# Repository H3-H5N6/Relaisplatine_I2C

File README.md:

# Beschreibung

8-fach Relaisplatine, die über I²C angesteuert wird. Die Relais werden dabei über eine separate Spannung versorgt.

Die I²C-Adresse muss durch entsprechende Brücken bei A0 - bis A2 ausgeält werden. Die Grundadresse des PCF 8475 ist 0x40 und de
ie des PCF 8475 ist 0x70.

Die LEDs bei den Relais leuchten, wenn die Relais in Ruhe sind. Des weiteren gibt es zwei Power-LEDs, einmal für die 5V vom I²C und einaml für die 5/12V der Relais.

Der Interrupt-Pin ist herausgezogen, aber nicht weiter beschaltet.

# Schaltplan

# Bestückungsplan

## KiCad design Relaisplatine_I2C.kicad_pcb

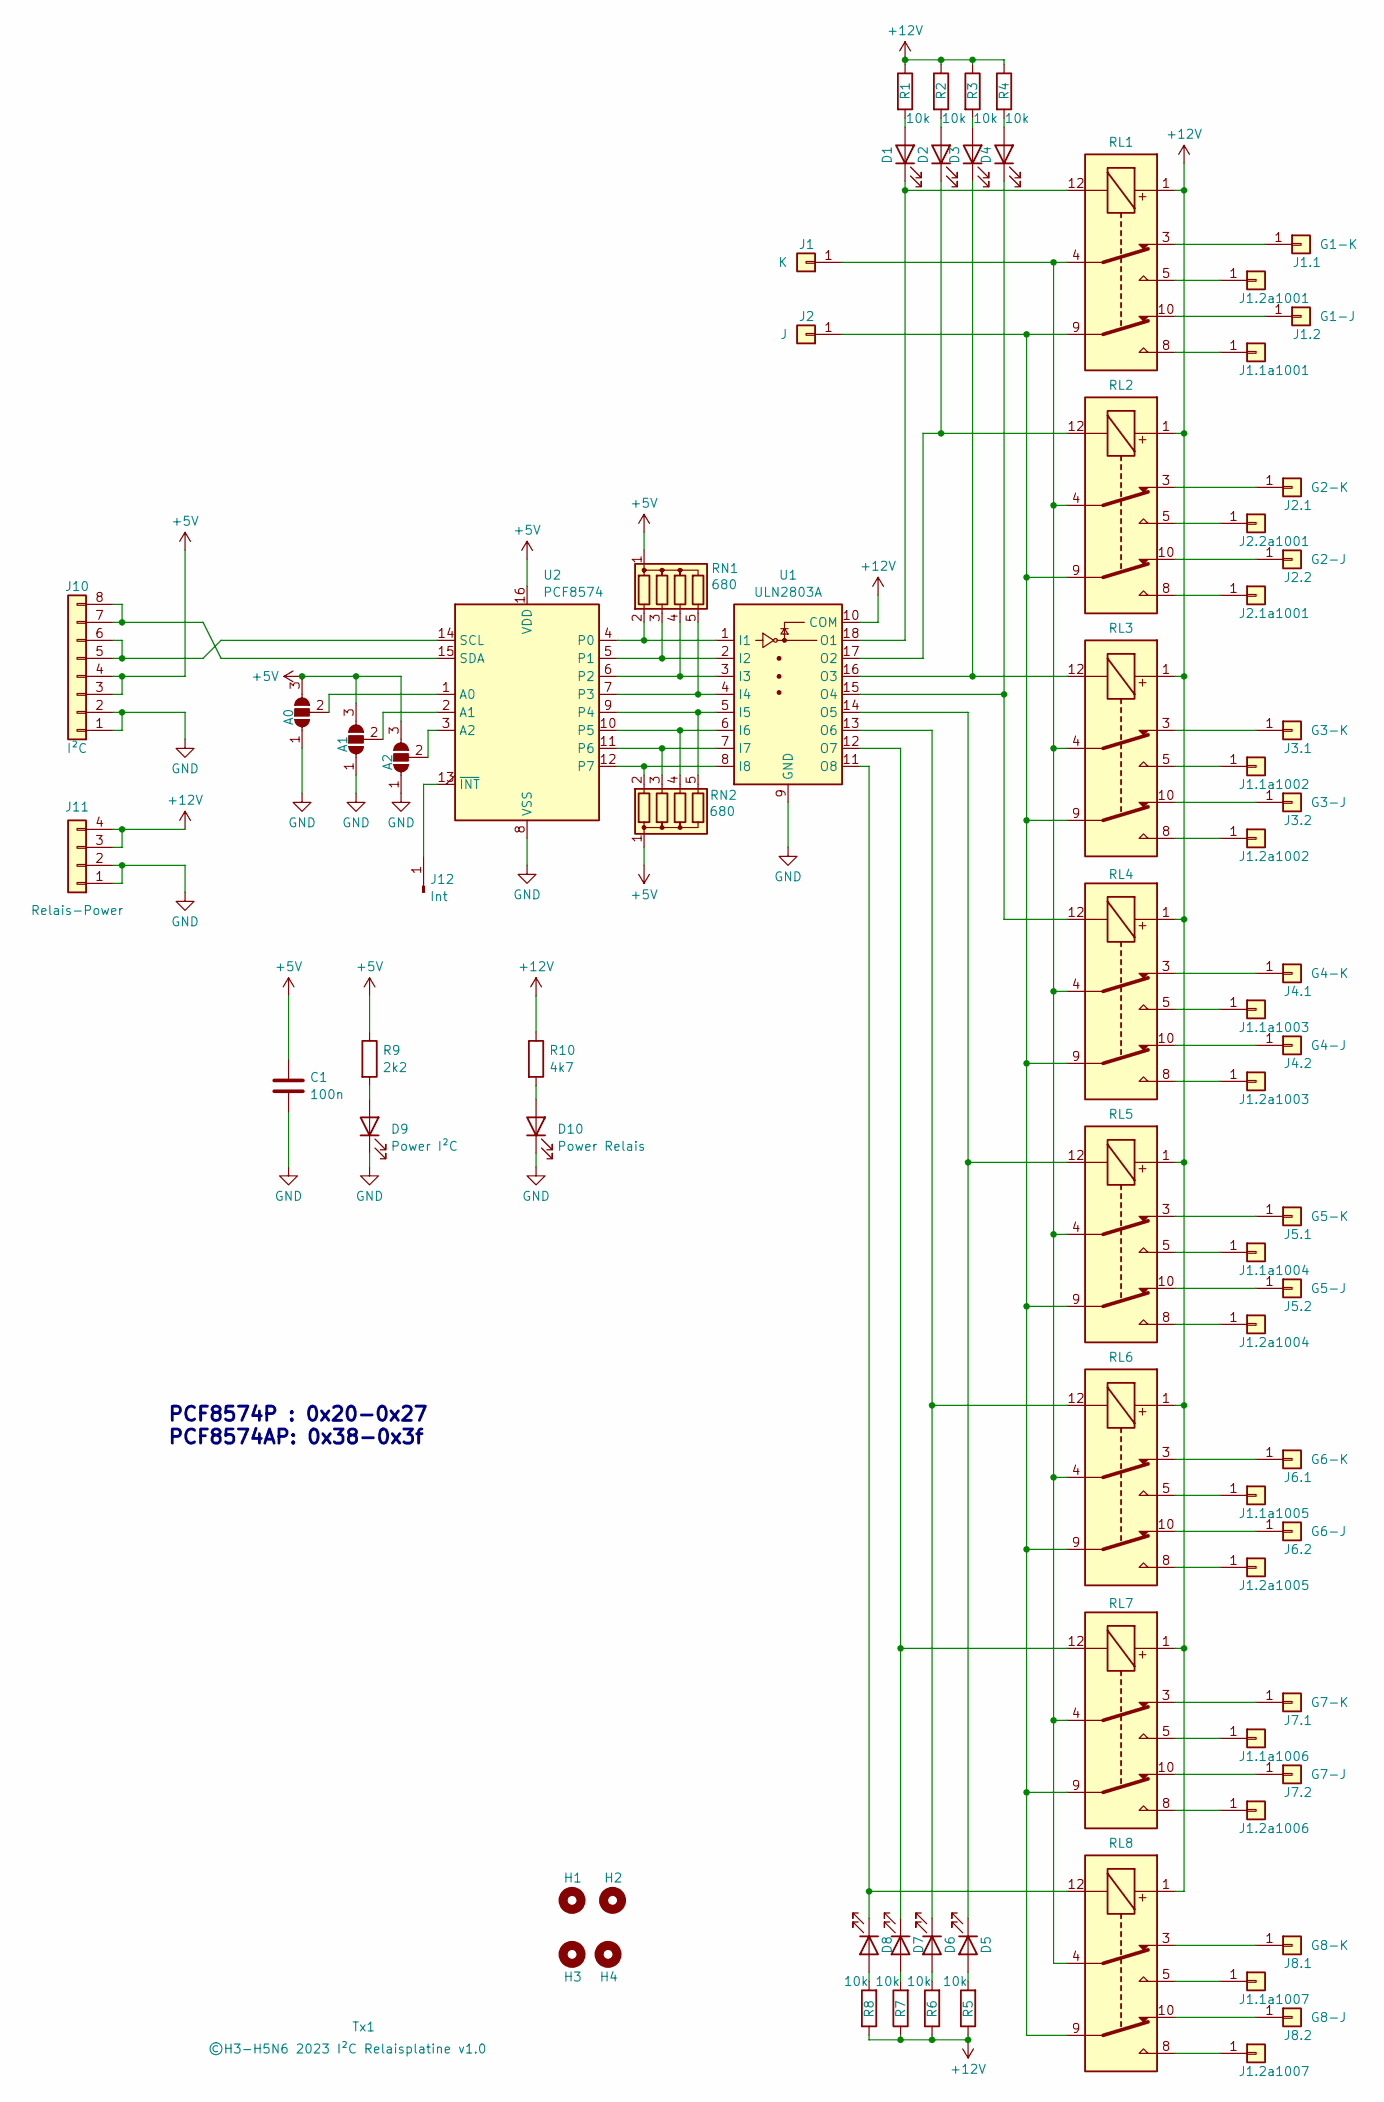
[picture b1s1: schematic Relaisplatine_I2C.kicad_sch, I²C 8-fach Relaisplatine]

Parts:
A0, A1, A2: SolderJumper_3_Open; SolderJumper-3_P1.3mm_Open_RoundedPad1.0x1.5mm
C1: 100n; C_Disc_D6.0mm_W2.5mm_P5.00mm
D1, D2, D3, D4, D5, D6, D7, D8: LED; LED_0805_2012Metric_Pad1.15x1.40mm_HandSolder
D9: Power I²C; LED_0805_2012Metric_Pad1.15x1.40mm_HandSolder
D10: Power Relais; LED_0805_2012Metric_Pad1.15x1.40mm_HandSolder
H1, H2, H3, H4: MountingHole; MountingHole_3.2mm_M3
J1: K; Pad_7.5x2.2mm
J1.1: G1-K; Pad_7.5x2.2mm
J1.1a1001, J1.2a1002, J1.2a1003, J1.2a1004, J1.2a1005, J1.2a1006, J1.2a1007, J2.1a1001: G1-J; Pin_D1.1mm_L8.5mm_W2.5mm_FlatFork
J1.1a1002, J1.1a1003, J1.1a1004, J1.1a1005, J1.1a1006, J1.1a1007, J1.2a1001: G1-K; Pin_D1.1mm_L8.5mm_W2.5mm_FlatFork
J1.2: G1-J; Pad_7.5x2.2mm
J2: J; Pad_7.5x2.2mm
J2.1: G2-K; Pad_7.5x2.2mm
J2.2: G2-J; Pad_7.5x2.2mm
J2.2a1001: G2-K; Pin_D1.1mm_L8.5mm_W2.5mm_FlatFork
J3.1: G3-K; Pad_7.5x2.2mm
J3.2: G3-J; Pad_7.5x2.2mm
J4.1: G4-K; Pad_7.5x2.2mm
J4.2: G4-J; Pad_7.5x2.2mm
J5.1: G5-K; Pad_7.5x2.2mm
J5.2: G5-J; Pad_7.5x2.2mm
J6.1: G6-K; Pad_7.5x2.2mm
J6.2: G6-J; Pad_7.5x2.2mm
J7.1: G7-K; Pad_7.5x2.2mm
J7.2: G7-J; Pad_7.5x2.2mm
J8.1: G8-K; Pad_7.5x2.2mm
J8.2: G8-J; Pad_7.5x2.2mm
J10: I²C; PinHeader_2x04_P2.54mm_Horizontal
J11: Relais-Power; PinHeader_2x02_P2.54mm_Horizontal
J12: Int; PinHeader_1x01_P2.54mm_Vertical
R1, R2, R3, R4, R5, R6, R7, R8: 10k; R_0805_2012Metric_Pad1.20x1.40mm_HandSolder
R9: 2k2; R_0805_2012Metric_Pad1.20x1.40mm_HandSolder
R10: 4k7; R_0805_2012Metric_Pad1.20x1.40mm_HandSolder
RL1, RL2, RL3, RL4, RL5, RL6, RL7, RL8: HFD3; HFD3+2005SD
RN1, RN2: 680; R_Array_SIP5
Tx1: ©H3-H5N6 2023 I²C Relaisplatine ${REVISION}; Text
U1: ULN2803A; DIP-18_W7.62mm
U2: PCF8574; DIP-16_W7.62mm

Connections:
+5V: A0.3 (B), A1.3 (B), A2.3 (B), C1.1, J10.3, J10.4, R9.1, RN1.1 (common), RN2.1 (common), U2.16 (VDD)
+12V: J11.3, J11.4, R1.1, R2.1, R3.1, R4.1, R5.1, R6.1, R7.1, R8.1, R10.1, RL1.1, RL2.1, RL3.1, RL4.1, RL5.1, RL6.1, RL7.1, RL8.1, U1.10 (COM)
GND: A0.1 (A), A1.1 (A), A2.1 (A), C1.2, D9.1 (K), D10.1 (K), J10.1, J10.2, J11.1, J11.2, U1.9 (GND), U2.8 (VSS)
unnamed: A0.2 (C), U2.1 (A0)
unnamed: A1.2 (C), U2.2 (A1)
unnamed: A2.2 (C), U2.3 (A2)
unnamed: D1.2 (A), R1.2
unnamed: D1.1 (K), RL1.12, U1.18 (O1)
unnamed: D2.2 (A), R2.2
unnamed: D2.1 (K), RL2.12, U1.17 (O2)
unnamed: D3.2 (A), R3.2
unnamed: D3.1 (K), RL3.12, U1.16 (O3)
unnamed: D4.2 (A), R4.2
unnamed: D4.1 (K), RL4.12, U1.15 (O4)
unnamed: D5.2 (A), R5.2
unnamed: D5.1 (K), RL5.12, U1.14 (O5)
unnamed: D6.2 (A), R6.2
unnamed: D6.1 (K), RL6.12, U1.13 (O6)
unnamed: D7.2 (A), R7.2
unnamed: D7.1 (K), RL7.12, U1.12 (O7)
unnamed: D8.2 (A), R8.2
unnamed: D8.1 (K), RL8.12, U1.11 (O8)
unnamed: D9.2 (A), R9.2
unnamed: D10.2 (A), R10.2
unnamed: J1.1, RL1.4, RL2.4, RL3.4, RL4.4, RL5.4, RL6.4, RL7.4, RL8.4
unnamed: J1.1.1, RL1.3
unnamed: J1.1a1001.1, RL1.8
unnamed: J1.1a1002.1, RL3.5
unnamed: J1.1a1003.1, RL4.5
unnamed: J1.1a1004.1, RL5.5
unnamed: J1.1a1005.1, RL6.5
unnamed: J1.1a1006.1, RL7.5
unnamed: J1.1a1007.1, RL8.5
unnamed: J1.2.1, RL1.10
unnamed: J1.2a1001.1, RL1.5
unnamed: J1.2a1002.1, RL3.8
unnamed: J1.2a1003.1, RL4.8
unnamed: J1.2a1004.1, RL5.8
unnamed: J1.2a1005.1, RL6.8
unnamed: J1.2a1006.1, RL7.8
unnamed: J1.2a1007.1, RL8.8
unnamed: J2.1, RL1.9, RL2.9, RL3.9, RL4.9, RL5.9, RL6.9, RL7.9, RL8.9
unnamed: J2.1.1, RL2.3
unnamed: J2.1a1001.1, RL2.8
unnamed: J2.2.1, RL2.10
unnamed: J2.2a1001.1, RL2.5
unnamed: J3.1.1, RL3.3
unnamed: J3.2.1, RL3.10
unnamed: J4.1.1, RL4.3
unnamed: J4.2.1, RL4.10
unnamed: J5.1.1, RL5.3
unnamed: J5.2.1, RL5.10
unnamed: J6.1.1, RL6.3
unnamed: J6.2.1, RL6.10
unnamed: J7.1.1, RL7.3
unnamed: J7.2.1, RL7.10
unnamed: J8.1.1, RL8.3
unnamed: J8.2.1, RL8.10
unnamed: J10.5, J10.6, U2.14 (SCL)
unnamed: J10.7, J10.8, U2.15 (SDA)
unnamed: J12.1, U2.13 (~INT)
unnamed: RN1.2 (R1), U1.1 (I1), U2.4 (P0)
unnamed: RN1.3 (R2), U1.2 (I2), U2.5 (P1)
unnamed: RN1.4 (R3), U1.3 (I3), U2.6 (P2)
unnamed: RN1.5 (R4), U1.4 (I4), U2.7 (P3)
unnamed: RN2.2 (R1), U1.8 (I8), U2.12 (P7)
unnamed: RN2.3 (R2), U1.7 (I7), U2.11 (P6)
unnamed: RN2.4 (R3), U1.6 (I6), U2.10 (P5)
unnamed: RN2.5 (R4), U1.5 (I5), U2.9 (P4)

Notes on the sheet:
PCF8574P : 0x20-0x27 PCF8574AP: 0x38-0x3f

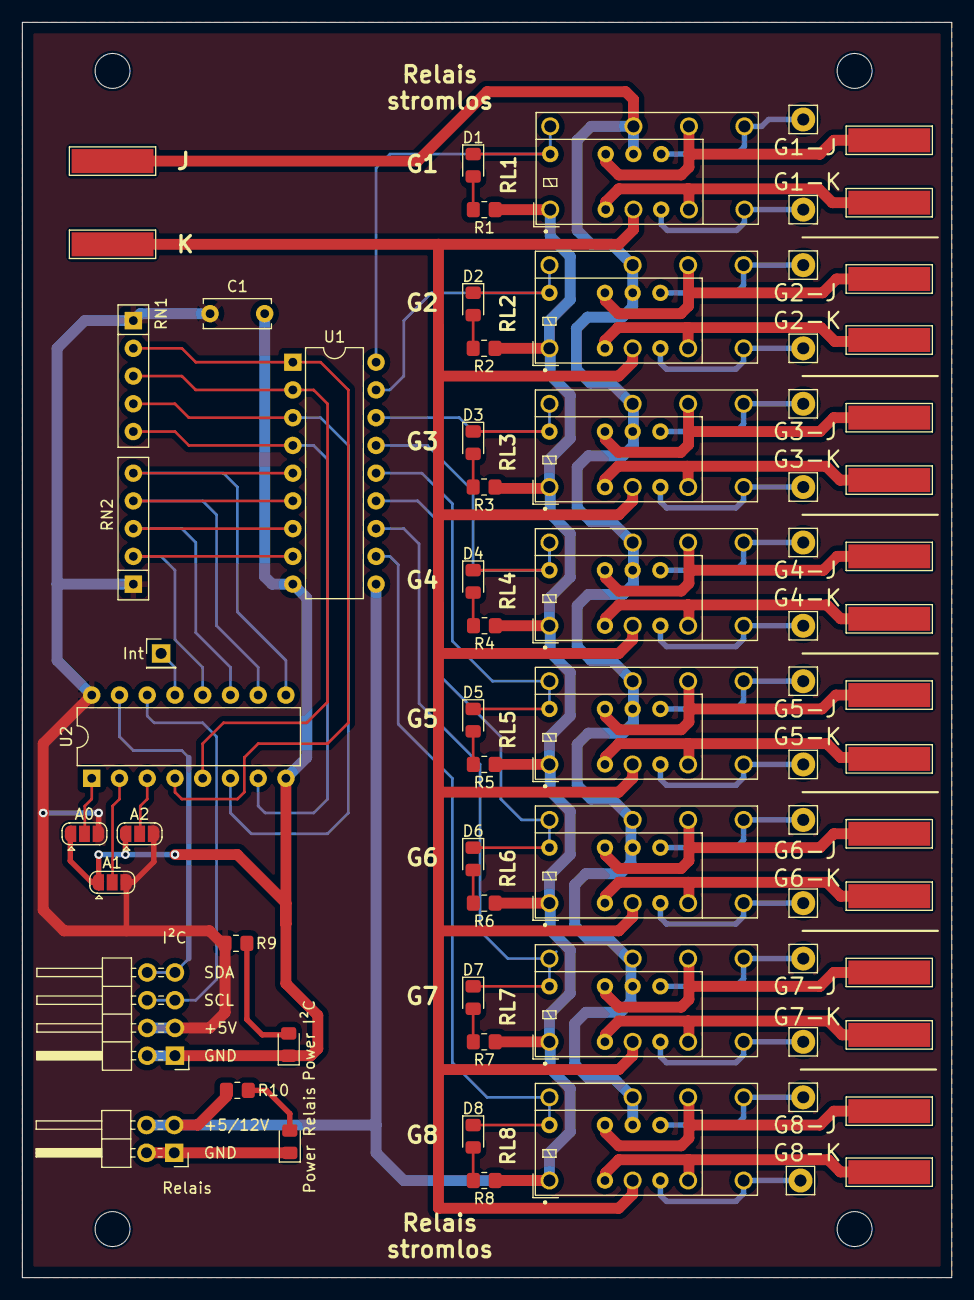
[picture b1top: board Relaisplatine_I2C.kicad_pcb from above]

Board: 2 copper layers, 85.1 x 114.9 mm, 78 parts (0 on the bottom side), 69 nets.

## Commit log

2023-11-20 Initial
2023-11-20 Readme und Schaltplan hinzugefügt
2023-11-20 Update Files
2023-11-20 Pins für A0-2 beschltet
2023-11-26 unkenannte Änderung
2023-11-26 Script zur automatsichen Aktualisierung der PDF im doc-Ordner
2023-11-26 pdf und svg nach doc doc verschoben
2023-11-26 Bilder landen jetzt in doc/
2023-11-26 Unbekannte Änderungen
2023-11-26 Fehlerbehandlung eingeführt
2023-11-26 schematic als pdf hinzugefügt
2023-11-27 Schema auch als png erzeugen und anzeigen
2023-11-27 Schemaic schwerz/weiß als svg erzeugen, trimm klappt nun
2023-11-27 Fix schematic svg
2023-12-03 .gitignore hinzugefügt
2023-12-04 Int-Pin herausgezogen und Kosmetik
2023-12-05 Beschriftung für Gx-J|K vergrößert
2023-12-12 .gitignore erweitert
2023-12-12 Power-LEDs für 5V und 12V hinzugefügt
2023-12-14 Revision als Feld, Widerstand der Ralais-LEDs auf 10k gesetzt
2023-12-15 Abstand Fläche - Plarineneand auf 1mm gesetzt
2024-04-08 Kosmetik

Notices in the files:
parts and their libraries:
©H3-H5N6 2023 I²C Relaisplatine v1.0
